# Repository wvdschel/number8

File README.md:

number8
=======

Number8 is the second iteration of our [WELEK robot sumo competition](http://ieeesb.elis.ugent.be/nl/welek/robot/2013) entry.
It is a differential wheeled robot, built out of Lego Technics and powered by 5 Lego Technic motors and a PIC18.

It is equiped with 8 input sources:

1. 2x analog infrared distance sensors on the front
2. 4x analog color sensors on the bottom, one on each corner of the robot, to detect the edge of the arena
3. 1x digital pressure sensor on the back, to detect an attack from behind (this sensor is colloqually referred to as "the butt-sex-detector").
4. 1x rotary encoder to measure our forward/backward movement

Media
-----

[A video featuring our first build, number7](http://www.youtube.com/embed/BkIkCT7gmbQ). It is the robot with double batteries and green-grey scoop. It is also the only robot consistently winning throughout the video, and the only one that does not recieve human help ;)

Since then, we have made the robot faster (a gear ratio change, resulting in a 9 times faster robot, at the cost of a 9 times lower torque).

We also replaced the scoop, since it was mechanically flawed and it on multiple occasions resulted in our robot being lifted off the ground with all but its last wheels. It now has a bumper made of wheels constantly pushing the enemy away.

The progress wheel was also not present in the first version.

Operating instructions
----------------------

As per the contest rules, the robot operates autonomously during combat. The only operations a meatbag assistant should perform is to start the robot. This is done as follows:

1. Put the robot down inside the arena. Make sure all corner sensors are inside the arena, and not on or over the edge. Also make sure that nothing is in front of the robot, since that would mess up the initial sensor calibration in the next step.
2. Press any button on the Dwengo board to calibrate the sensors. Whatever is under the ground sensors will be considered as the color of the arena, and the distance sensor values will be considered "infinite distance" values.
3. Press the north or south buttons to start the robot in forward drive mode, or left or right to have it perform a flanking operation.
4. Watch it destroy the competition.

Code
----
We started from a modified version of the "sumolib" provided by the contest organization. We modified it to use our motor controller and to print to serial instead of the LCD.

Most of the logic is contained in aiLib.c. The robot operates as a state machine, switching between a search state, a destroy state, a flanking state and a survival state based on its sensor readings. Transitions can easily be found by searching for `SWITCH_STATE`.

The `sumolib` directory contains the modified version of the sumolib we use, while `quadenclib` contains code we plucked off the internet (TODO: add link) for using our rotary encoder.

Debugging
---------

There are two debugging methods available: serial prints and LEDs 4 trough 7 on the Dwengo board.

### Serial debugging
Serial debugging is enabled by setting `DEBUG` to `1` in `serialDebug.h`.

Since the motor controller is being operated over serial as well, we also have some garbage from the motor commands on the serial, and we can't print high bytes.

### LED debugging
The four last LEDs of the Dwengo board indicate the state the robot is in:

	 LD7 LD6 LD5 LD4 LD3 LD2 LD1 LD0
	/-------------------------------\
	| o   o   o   o   o   o   o   o |
	\-------------------------------/
	  |   |   |   |       |   |_ Rotary encoder feedback
	  |   |   |   |       |_____ Rotary encoder feedback
	  |   |   |   |_____________ Flashes when a stall is detected
	  |   |   |_________________ STATE_SEEK
	  |   |_____________________ STATE_DESTROY
	  |_________________________ STATE_SURVIVE

If both LD5 and LD6 are lit, the robot is in `STATE_FLANK`.

Component references
--------------------

Rotary encoder: [Sparkfun - COM-09117](https://www.sparkfun.com/products/9117)
Long range sensors: [Sharp GP2Y0A21YK0F](http://ieeesb.elis.ugent.be/sites/ieeesb.elis.ugent.be/files/gp2y0a21yk_e.pdf)
Ground sensors: [Vishay TCRT5000](http://ieeesb.elis.ugent.be/sites/ieeesb.elis.ugent.be/files/tcrt5000.pdf)

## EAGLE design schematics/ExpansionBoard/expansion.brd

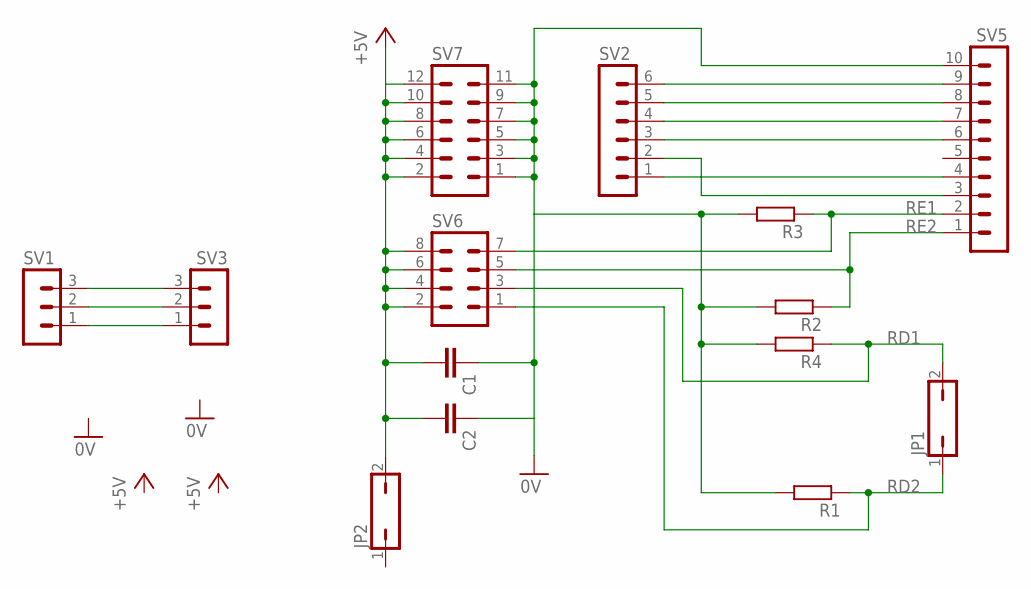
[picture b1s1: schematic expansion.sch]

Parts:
C1, C2: C-EU025-030X050; C025-030X050
JP1, JP2: JP1Q; JP1
R1: R-EU_0207/10; 0207/10
R2: R-EU_0207/5V; 0207/5V
R3: R-EU_0207/2V; 0207/2V
R4: R-EU_0204/7; 0204/7
SV1, SV3: MA03-1
SV2: MA06-1
SV5: MA10-1
SV6: MA04-2
SV7: MA06-2

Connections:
0V: C1.1, C2.1, R1.2, R2.2, R3.2, R4.2, SV5.10, SV7.1, SV7.3, SV7.5, SV7.7, SV7.9, SV7.11
+5V: C1.2, C2.2, JP2.2, SV6.2, SV6.4, SV6.6, SV6.8, SV7.2, SV7.4, SV7.6, SV7.8, SV7.10, SV7.12
unnamed: SV2.6, SV5.9
unnamed: SV2.5, SV5.8
unnamed: SV2.4, SV5.7
unnamed: SV2.3, SV5.6
unnamed: SV1.3, SV3.3
unnamed: SV1.2, SV3.2
unnamed: SV1.1, SV3.1
unnamed: SV2.1, SV5.4
unnamed: SV2.2, SV5.3
RD1: JP1.2, R4.1, SV6.3
RD2: JP1.1, R1.1, SV6.1
RE1: R3.1, SV5.2, SV6.7
RE2: R2.1, SV5.1, SV6.5

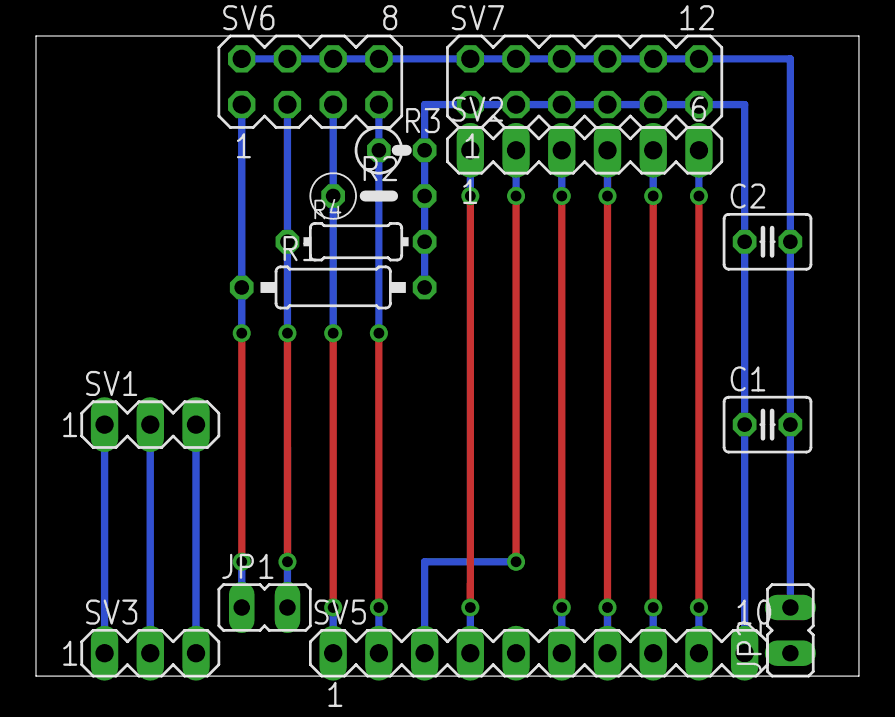
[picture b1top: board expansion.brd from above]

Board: 2 copper layers, 45.7 x 35.6 mm, 14 parts (0 on the bottom side), 15 nets.

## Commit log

2013-03-04 Initial number7 import
2013-03-17 - added schematics - added initial code to support progress wheel - refactored some code - removed some unnecessary files
2013-03-17 made git ignore some linker files and files containing compiler warnings/errors
2013-03-18 added modified version of quadrature encoder for progress wheel (http://www.pavius.net/2010/02/rotary-encoder-based-cooking-timer/)
2013-03-22 -added main microcontroller datasheet -modified quadrature encoder code for our specific extension board
2013-04-18 Added my local paths to the projects include paths, so it will build on my PC
2013-04-18 Added progress wheel readout to sensor readings.
2013-04-18 Made the robot wait 4600ms instead of 5000ms during countdown.
2013-04-19 Motors have been swapped during reconstruction.
    I fixed the code accordingly.
2013-04-19 Support for black edge white arena.
    Also adjusted the timings for the faster gear ratio to not go completely
    beserk.
2013-04-19 Bugfix in initial ground sensor debug print.
2013-04-19 Rear and front left ground sensors were swapped.
2013-04-19 Made survive-mode last longer to handle high speed
    With the new gear ratio, the robot sometimes goes over the edge of the
    arena with the front sensors before going into survival mode. Because of
    the short duration of the survival mode, the robot is not able to break
    and alter direction for long enough to back up to the arena edge.
    This caused the robot to halt briefly after crossing the line, before
    continuing on its way out of the arena.
2013-04-21 Stop pushing if the progress wheel says we're not making progress.
    Additionally, the progress variable now reports positive values for
    forward movement, and negative values for backward movement.
2013-04-21 Removed DESTROY_OVER state and added FLANK state.
    Also modified distance sensor values to have a wider range and hopefully
    higher accuracy.
2013-04-21 Added initialEyeAvg variable.
2013-04-21 Fixed LED state indication and slowed down debug mode.
2013-04-21 Seperated sensor calibration and robot startup
    First keypress calibrates sensors, second keypress starts the robot.
2013-04-21 Fixed line endings
2013-04-21 Added readme
2013-04-21 Fixed some typos and formatting.
2013-04-21 More formatting fixes.
2013-04-21 Added scrolling window history for progress wheel measurements, since 15ms isn't a very meaningful sample rate.
2013-04-21 Added video of number7
2013-04-21 Fixed youtube link
2013-04-21 Fixed typo
2013-04-21 Added rotary encoder link to readme
2013-04-21 Added LED feedback for sensor calibration success
2013-04-21 Broke everything?
2013-04-21 Modified state LED update to preserve non-state LEDS
2013-04-22 Made project build without hardcoded library folders.
2013-04-23 Made lack of progress stop spamming
2013-04-23 Made rear pressure sensor halt the robot while pressed.
2013-04-23 Fixed formatting of initial ground sensor prints.
2013-04-23 Added testing routines
2013-04-23 Made serial/MC use POLULU so we can debug while driving
2013-04-23 Made sensor calibration only use the center button.
2013-04-23 Changed print format, and only print progress window every 100 turns.
2013-04-24 Removed motor debug prints to prevent UART spam
2013-04-24 Moved USE_MOTORS to be in the same place as DEBUG
2013-04-24 Reduced progress wheel history windows size.
2013-04-24 Fixed off-by-one bug for forward motion on the progress wheel
2013-04-24 Added a bunch of robot tests
2013-04-26 Added sensor spec links
2013-04-26 Added cfokets's Q&D debug GUI
2013-04-26 reordered sensors
2013-04-26 the colors are so pretty
2013-04-26 Rewrote driveUntilWhite to log long distance sensors
2013-04-26 parse ground sensor states
2013-04-26 removed old code
2013-04-27 Removed left-over debugging code from the left engine.
2013-04-27 Enabled motors
2013-04-27 Added tests for braking using only long distance sensors & initial PoC code for flanking manouver
2013-04-27 Increased progress thresshold & time between turns
2013-04-28 Added unused printBase64 function
2013-04-28 Removed 'EXTERMINATE' print at startup
2013-04-28 Removed leftover garbage in serialDebug.c
2013-04-28 Compressed state prints for lower latency and allowing more frequent prints
2013-04-28 Updated log parser to allow reading of new print format.
2013-04-29 Started work on the new state machine
2013-04-29 Fixed syntax error in input parsing
2013-04-29 Removed push sensor from survivalCheck
2013-04-29 Fixed chatter on UART by motor codes
2013-04-29 fixed gui after Wim's changes
2013-04-29 added speedometer
2013-04-29 Changes at test night
2013-04-29 A night of debugging
2013-04-30 Added state display to the gui
2013-05-01 Swapped rear sensors
2013-05-01 Pre contest hacking session
